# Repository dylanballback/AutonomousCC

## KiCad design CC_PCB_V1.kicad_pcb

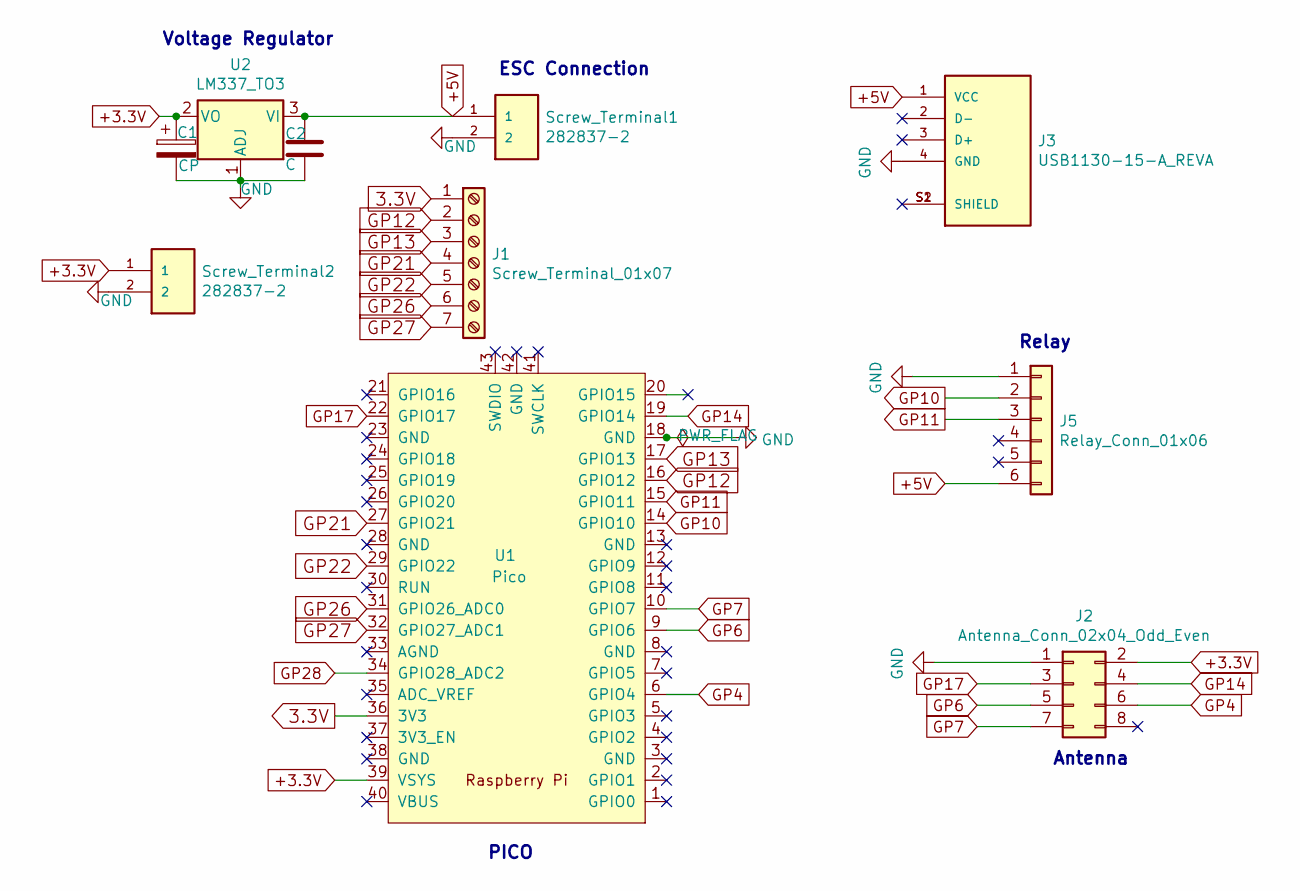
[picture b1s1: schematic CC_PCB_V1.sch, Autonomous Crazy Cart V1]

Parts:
C1: CP; CP_Radial_D8.0mm_P5.00mm
C2: C; CP_Radial_D8.0mm_P5.00mm
J1: Screw_Terminal_01x07; TerminalBlock_TE_282834-7_1x07_P2.54mm_Horizontal
J2: Antenna_Conn_02x04_Odd_Even; PinHeader_2x04_P2.00mm_Vertical
J3: USB1130-15-A_REVA; GCT_USB1130-15-A_REVA; PARTREV A
J5: Relay_Conn_01x06; PinHeader_1x06_P2.00mm_Vertical
Screw_Terminal1, Screw_Terminal2: 282837-2; TE_282837-2
U1: Pico; RPi_Pico_SMD_TH
U2: LM337_TO3; SOT230P696X180-4N

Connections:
3.3V: J1.1, U1.36 (3V3)
+3.3V: C1.1, J2.2, Screw_Terminal2.1, U1.39 (VSYS), U2.2 (VO)
+5V: C2.1, J3.1 (VCC), J5.6, Screw_Terminal1.1, U2.3 (VI)
GND: C1.2, C2.2, J2.1, J3.4 (GND), J5.1, Screw_Terminal1.2, Screw_Terminal2.2, U1.18 (GND), U2.1 (ADJ)
GP4: J2.6, U1.6 (GPIO4)
GP6: J2.5, U1.9 (GPIO6)
GP7: J2.7, U1.10 (GPIO7)
GP10: J5.2, U1.14 (GPIO10)
GP11: J5.3, U1.15 (GPIO11)
GP12: J1.2, U1.16 (GPIO12)
GP13: J1.3, U1.17 (GPIO13)
GP14: J2.4, U1.19 (GPIO14)
GP17: J2.3, U1.22 (GPIO17)
GP21: J1.4, U1.27 (GPIO21)
GP22: J1.5, U1.29 (GPIO22)
GP26: J1.6, U1.31 (GPIO26_ADC0)
GP27: J1.7, U1.32 (GPIO27_ADC1)
GP28: U1.34 (GPIO28_ADC2)
unnamed: J3.S1 (SHIELD), J3.S2 (SHIELD)

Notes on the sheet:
Antenna
Relay
PICO
ESC Connection
Voltage Regulator

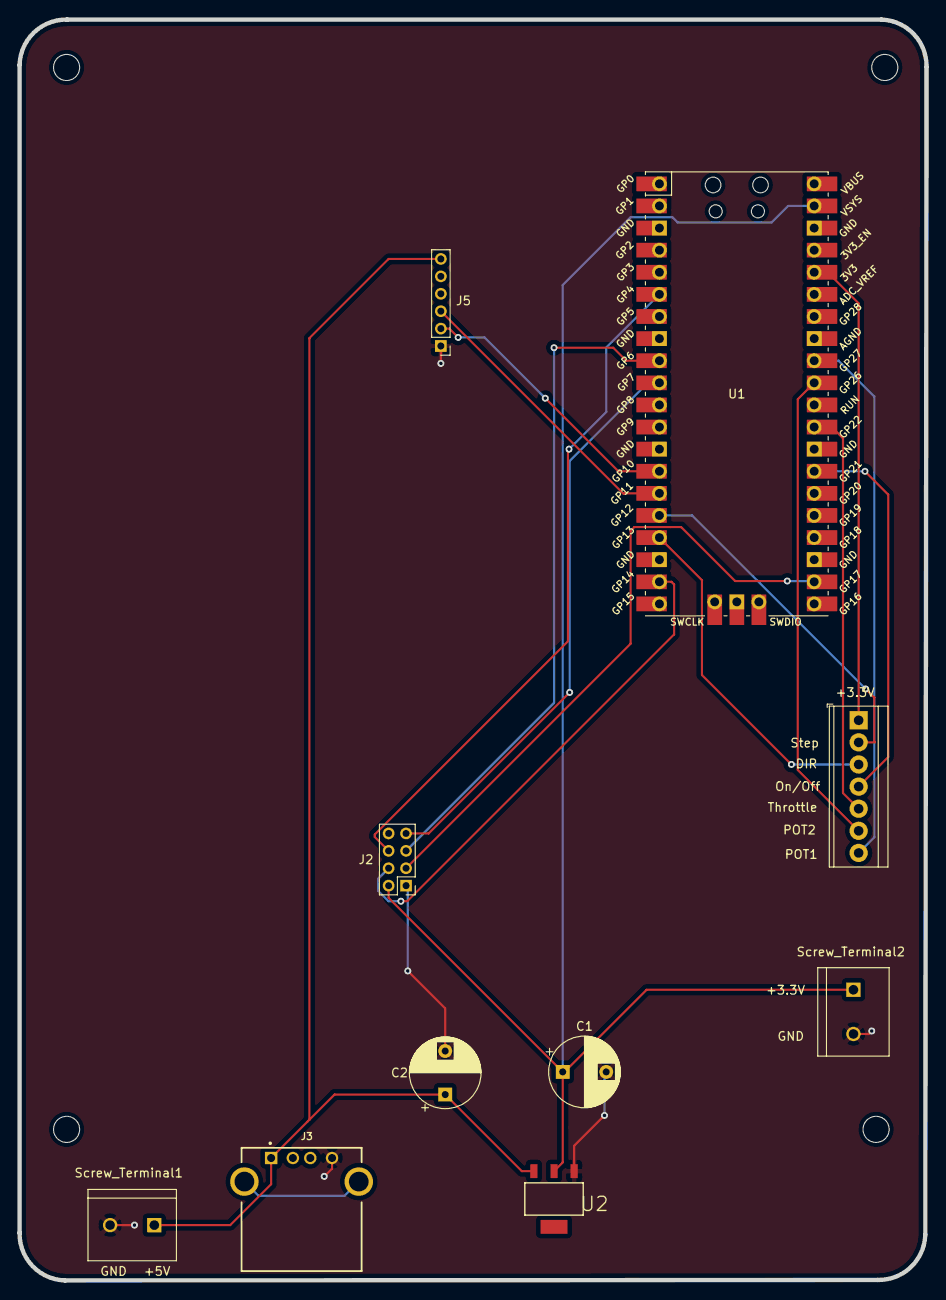
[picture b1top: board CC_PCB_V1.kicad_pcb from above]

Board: 2 copper layers, 104.2 x 144.9 mm, 14 parts (0 on the bottom side), 18 nets.

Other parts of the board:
H1, H2, H3, H4: MountingHole; MountingHole_3mm

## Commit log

2021-09-03 Added Terminal Blocks Link to List
2021-09-03 Rename Parts_List_and_Links to Parts_List_and_Links.md
2021-09-03 Small add
2021-09-03 Added Symbols and Footprint
2021-09-03 Update Schematic
    Added Linear Voltage Reg and USB connector
2021-09-03 Update Library
2021-09-03 Added footprints
2021-09-03 Trying to fix 2 errors from DRC
    Related to power > Lady Bug
2021-09-04 Auto stash before merge of "main" and "origin/main"
2021-09-04 Wiring Board
    I tried my best here, let me know what you think.
2021-09-06 Updated Screw Terminal Block
2021-09-06 Updated Circuit Wiring
2021-09-06 Saved As Gerber File
2021-09-07 Completed V1 PCB
2021-09-17 Version 2 of PCB
    editing wiring, changing voltage regulator, and adding screw terminals.
2021-09-18 Finished SCH and added components to PCB
2021-09-18 "Finished" PCB
2021-09-21 Pushing so I can edit on my PC
2021-09-21 "Finished" PCB
    Re did the layout of the board for a better fitment
2021-09-21 Added 1x2 screw terminal for the POTS
2021-09-21 Added mounting holes
2021-09-21 Created Gerber file
2021-09-21 removed for merge
2021-09-21 removing all for version update and merging of branches with conflicting files.
